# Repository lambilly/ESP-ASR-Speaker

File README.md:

# ESP-ASR-Speaker · 翻页时钟 + 离线语音 + 蓝牙音箱

> 基于 **ESP32-WROVER-E (N16R8)** 与 **ASRPRO 2.0** 的桌面智能音箱：
> 铝合金翻页时钟音箱外壳 + 离线语音识别 + HA TTS 播报 + 蓝牙 A2DP + 30 颗 WS2812 状态灯。
>
> 项目首发于『瀚思彼岸』论坛：[【阿木制作】集翻页时钟、离线语音、蓝牙音箱、TTS、WiFi 和彩灯音箱](https://bbs.hassbian.com/forum.php?mod=viewthread&tid=33323)

---

## 这个项目做了什么

一块自制的 ESP32 主板塞进现成的铝合金音箱壳里，把四件东西合成一台：

- **ESP32** 负责音频流、蓝牙接收、灯效状态机、IO 控制
- **ASRPRO** 专门做离线语音识别，识别结果通过 UART 发给 ESP32
- ESP32 再联动 **Home Assistant / Node-RED** 触发场景（说一句"关灯"，HA 执行 + TTS 回一句"好的，已为您关灯"）
- 不开 HA 也能当**普通蓝牙音箱**用

## 功能特性

| 功能 | 说明 |
|---|---|
| 离线语音输入 | ASRPRO 本地识别，不联网、隐私安全、响应快 |
| HA 语音播报 | ESPHome `media_player` 接入 HA Edge TTS 等服务，MP3 流式播放 |
| 蓝牙音箱模式 | `a2dp_sink` 组件，手机连上就放歌 |
| 翻页屏时钟 | 81×26mm 彩色翻页时钟，全时段在线显示 |
| 状态指示灯 | 30 颗 WS2812，用颜色 + 呼吸/渐变表达 9 种系统状态 |
| 物理按键 | 两颗面板键做短按/长按分层：灯带开关、亮度三档、静音、蓝牙切换 |
| 过热保护 | DS18B20 测箱内温度，>50℃ 橙色呼吸提示 |
| 电池供电 | 18650 + IP5306，Type-C 充电，拔电可用 |

🎬 效果视频：[docs/images/demo.mp4](docs/images/demo.mp4)

---

## 硬件设计

### 主要器件

| 模块 | 型号 | 作用 |
|---|---|---|
| 主控 | ESP32-WROVER-E **N16R8**（16MB Flash + 8MB PSRAM） | 音频调度、灯光、IO |
| 语音 | ASRPRO **2.0** 核心板 4M | 离线识别 + 本地 TTS |
| 功放 | MAX98357A（I2S 数字功放） | 4Ω10W 喇叭驱动 |
| 电源 | IP5306 升压充放电一体板（**需升级版常开模式，2A 以上**） | 5V 供电 + 电池充电 |
| 灯带 | WS2812 × 30（GRB） | 全系统状态指示 |
| 温度 | DS18B20 | 箱体过热保护 |
| 按键 | 12mm 带灯非自锁 ×2 + 自锁 ×1 | 灯光/亮度、静音/蓝牙、总电源 |
| 阻容 | 10kΩ ×2（按键上拉）、220Ω ×1（灯带串联）、470μF + 0.1μF（滤波） | 全直插，方便新手焊接 |

### 引脚分配

| 功能 | GPIO | 备注 |
|---|---|---|
| UART TX / RX（ASRPRO） | 14 / 13 | 115200 8N1 |
| I2S BCLK / LRCK / DOUT | 27 / 26 / 25 | MAX98357A |
| MAX98357 `SD_MODE` | 22 | 低电平 = 硬件静音 |
| WS2812 数据 | 19 | 串联 220Ω 到灯带 DIN |
| DS18B20 | 32 | 单总线，4.7K 上拉 |
| LED 键 | 34 | **必须外部 10k 上拉** |
| Mode 键 | 35 | **必须外部 10k 上拉** |

### 外壳与结构件

外壳、翻页时钟屏、WS2812 灯带都来自网上现成的**铝合金翻页时钟音箱**套件，本项目只重做了内部主板：

- 铝合金箱体 **70×70×120mm**，带透光板、透光喇叭托环、透光振膜
- 彩色翻页时钟屏 **81×26mm**
- 哈曼 4Ω10W 全频喇叭
- 18650 电池包、止震贴、配重块

> 结构件图纸（STL）后续单独放出；壳体属第三方商品，本项目不附带其图纸与商品图。
>
> 本文中的成品照片与演示视频均为作者本人拍摄，不含第三方商品图。

### PCB 状态

- 板框 **84 × 53 mm**，**2 层板**，全直插 + 拔插式核心板（方便升级）
- 原理图已通过 ERC；**布线尚未完成、GND 未铺铜，暂不提供 Gerber**，请勿直接打样
- ⚠️ 1.0 版打样板**两个开关的原理图画错了**，当时飞线解决；2.0 版板已在嘉立创下单，验证后再放工程图

用 **KiCad 10** 打开 `hardware/ESP-ASR-Speaker.kicad_pro`。

| 原理图 | PCB 预览 |
|---|---|
| [docs/schematic.pdf](docs/schematic.pdf) |  |

---

## 固件（ESPHome）

### 音频管线：单管线 + 双音源

为了把 HA TTS 和蓝牙音频塞进同一套音频栈，用 `speaker_source` 平台，把蓝牙音源与 HTTP 音源放进**同一条管线**：

```yaml
media_player:
  - platform: speaker_source
    media_pipeline:
      speaker: max98357_speaker
      sources: [ a2dp_source, http_source ]
      format: MP3
```

> 试过双管线混音，底层音频流格式必然冲突（`Incompatible audio streams`），最终改成单管线双媒体源；HA 侧强制转码 MP3 单声道。

### LED 状态对照

| 颜色 | 状态 |
|---|---|
| 白色闪烁 | 上电开机动画（亮度压到 45%，避开电源输出上限） |
| 绿色常亮 | 空闲待机 |
| 青色呼吸 | 正在拾音 LISTEN（3 秒无新指令自动回待机） |
| 彩虹渐变 | TTS 播报中 |
| 蓝色呼吸 | 蓝牙音箱模式 |
| 紫红常亮 | 已静音 |
| 橙色呼吸 | 箱内温度 > 50℃ |
| 红色**呼吸** | OTA 升级中 |
| 红色**常亮** | WiFi 掉线 |

当前优先级：**灯带关闭 > 静音 > 过热 > 蓝牙 > TTS 播报 > 待机**

### 按键

| 操作 | LED 键（GPIO34） | Mode 键（GPIO35） |
|---|---|---|
| 短按 | 开/关灯带 | 硬件静音开/关（拉低 SD_MODE） |
| 长按 ≥0.8s | 亮度循环 100% → 50% → 25% | 蓝牙模式开/关 |

### 部署

```bash
cd firmware
cp secrets.yaml.example secrets.yaml   # 填 WiFi / API 密钥
esphome run esp-asr-speaker.yaml
```

首次烧录用 USB（板型 `esp32-wrover-kit`，esp-idf 框架，PSRAM quad 80MHz），之后走 OTA。

外部组件（首次编译自动从 GitHub 拉取）：

```yaml
external_components:
  - source: github://MexHigh/ESPHome-UART-Read-Line-Sensor   # 串口按行收指令
  - source: github://PxPert/a2dp_sink@master                 # 蓝牙 A2DP 接收
```

---

## ⚠️ 避坑指南（照着做能少烧几块板）

**1. 灯带线色是反的，别按"红正黑负"接**

> 红 = **GND**，黄 = **+5V**，黑 = **DATA**

不是"红正黑负"。我第一次没查卖家说明、只问了 AI，结果**烧了灯带和带灯开关**（灯带剪掉两颗还能用，开关报废）。接线前务必量一下。

**2. GPIO34 / 35 没有内部上拉**

必须外接 10kΩ 到 3.3V，悬空会乱触发。反过来，**不要**在按键两端并 0.1μF 电容——ESPHome 的 `delayed_on: 30ms` 软件消抖足够，硬件电容反而干扰。

**3. 灯带数据线串 220Ω**

GPIO19 与灯带 DIN 之间串 220~470Ω，防止信号反射烧掉第一颗灯珠。还要确保 ESP32 与灯带**共地**。

**4. 电源别小马拉大车**

功放遇到鼓点瞬间压降会让 ESP32 直接重启。IP5306 2.4A 已经是下限，条件允许上 3A/5A 升降压模块。
MAX98357A 的 VIN–GND 就近并 **470μF 以上**电解电容，灯带供电端并 **100μF 以上**。

**5. 蓝牙断开后重连不上**

`http_request: verify_ssl: false`，并且不要在代码里反复调 `stop()`，直接用 switch 实体控制蓝牙开关。

**6. TTS 没声音**

先查 HA 的 ffmpeg 是否正常，再把 `audio_http` 的 `buffer_size` 降下来。

**7. `minimum_chip_revision: "3.1"`**

按手上这块 WROVER 的批次写死的，换芯片批次先删掉这行，否则拒刷。日志默认 `WARN`，首刷排查时临时改 `INFO`。

---

## 目录结构

```
├─ hardware/                  KiCad 工程（原理图 / PCB / 工程配置）
├─ firmware/
│  ├─ esp-asr-speaker.yaml    ESPHome 主配置
│  ├─ secrets.yaml.example    密钥模板
│  └─ components/             自定义头文件（串口指令解析 / LED 状态机）
├─ docs/
│  ├─ schematic.pdf           原理图导出
│  ├─ pcb-top.svg             PCB 预览
│  ├─ bom.csv                 元件清单（不含价格）
│  └─ images/                 成品图与演示视频
├─ LICENSE
└─ README.md
```

## 物料清单

元件清单见 [docs/bom.csv](docs/bom.csv)（型号 / 封装 / 数量，不含采购价格）。
结构件另需：70×70×120 铝合金壳体、81×26mm 翻页时钟屏、哈曼 4Ω10W 喇叭、透光振膜与托环、18650 电池、止震贴、配重块。

## 已知问题 / Roadmap

- [x] 原理图 ERC 清零、35 个元件封装分配完毕
- [ ] **完成 PCB 布线 + GND 铺铜，出 Gerber**（当前不提供打样文件）
- [ ] 2.0 版板卡验证（1.0 版两个开关原理图画错，靠飞线救回）
- [ ] 结构件 STL 图纸整理后放出
- [ ] 补 `use_address`，解决 OTA mDNS 解析问题
- [ ] 第二台复刻验证（芯片批次、按键手感）

## 致谢

- 外壳与结构件：**铝合金翻页时钟音箱**套件
- [MexHigh/ESPHome-UART-Read-Line-Sensor](https://github.com/MexHigh/ESPHome-UART-Read-Line-Sensor)
- [PxPert/a2dp_sink](https://github.com/PxPert/a2dp_sink)
- ESPHome / KiCad / 瀚思彼岸社区

## 免责声明

DIY 锂电池供电设备存在**短路起火风险**，请在接线无误、绝缘良好的前提下通电测试。作者不对任何复制过程中的损失负责。

## License

[MIT](LICENSE) © 2026 lambilly

> 固件与硬件设计文件同用 MIT。第三方件（ASRPRO 语音模型、翻页时钟模块、铝合金外壳）遵循其各自的授权。

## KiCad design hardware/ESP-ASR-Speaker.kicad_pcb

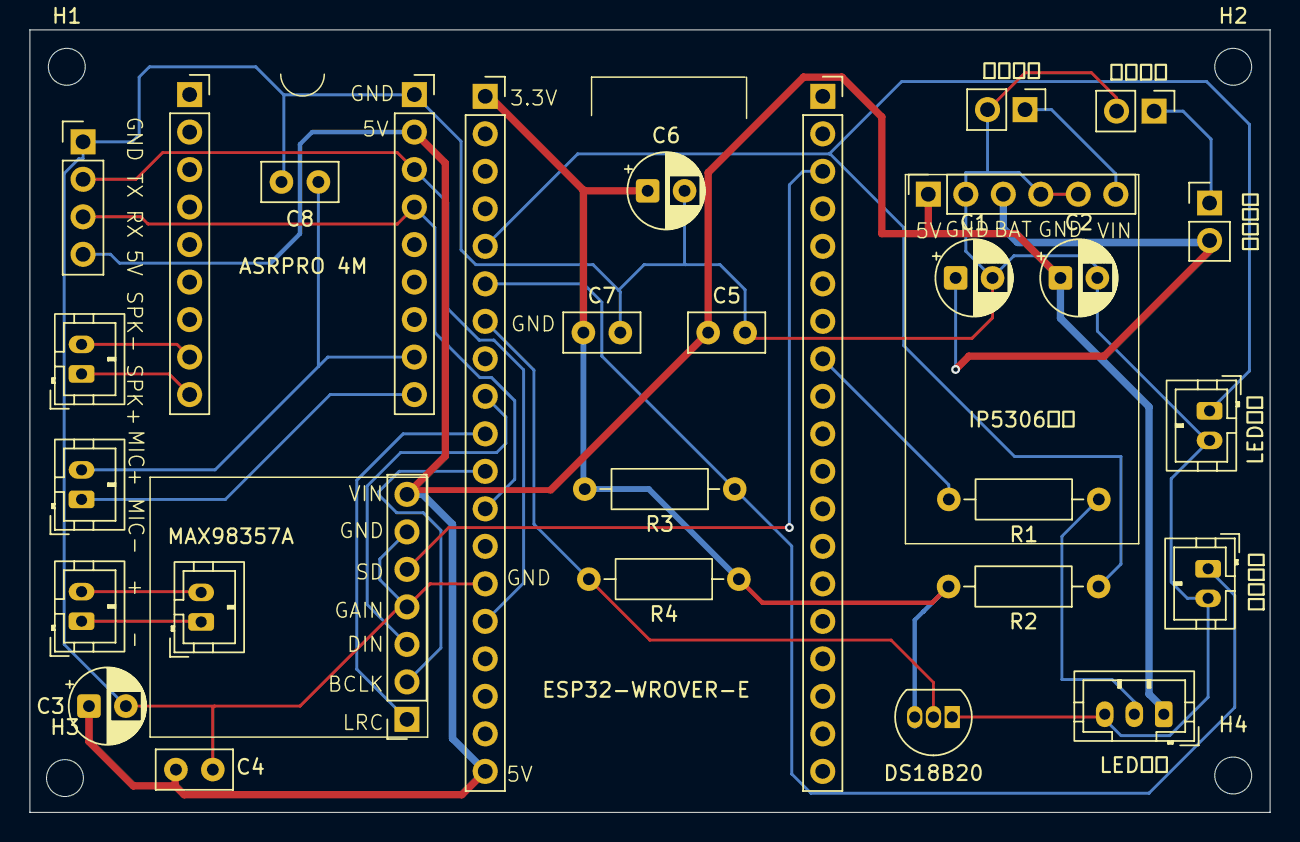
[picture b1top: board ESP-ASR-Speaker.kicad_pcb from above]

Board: 2 copper layers, 84.0 x 53.0 mm, 34 parts (0 on the bottom side), 23 nets.

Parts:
C1, C3, C6: 10μF; CP_Radial_D5.0mm_P2.50mm
C2: 22μF; CP_Radial_D5.0mm_P2.50mm
C4, C5, C7, C8: 0.1μF; C_Disc_D5.0mm_W2.5mm_P2.50mm
H1, H2, H3, H4: MountingHole; MountingHole_2.5mm
J1: MAX98357A; PinSocket_1x07_P2.54mm_Vertical
J_ASRA1: ASRPRO 4M; PinSocket_1x09_P2.54mm_Vertical
J_ASRB1: PinSocket_1x09_P2.54mm_Vertical
J_ASR_SPK1: SPK; JST_PH_B2B-PH-K_1x02_P2.00mm_Vertical
J_ASR_UART1: ASRPRO TTL; PinHeader_1x04_P2.54mm_Vertical
J_BATT1: 电池输入; PinHeader_1x02_P2.54mm_Vertical
J_BATT_SW1: 电池开关; PinHeader_1x02_P2.54mm_Vertical
J_ESPA1: ESP32-WROVER-E; PinSocket_1x19_P2.54mm_Vertical
J_ESPB1: Conn_01x19_Socket; PinSocket_1x19_P2.54mm_Vertical
J_KEY_SW1: LED开关; JST_PH_B2B-PH-K_1x02_P2.00mm_Vertical
J_KEY_SW2: 功能开关; JST_PH_B2B-PH-K_1x02_P2.00mm_Vertical
J_LED_BUS1: LED灯带; JST_PH_B3B-PH-K_1x03_P2.00mm_Vertical
J_MIC1: MIC; JST_PH_B2B-PH-K_1x02_P2.00mm_Vertical
J_POWER1: IP5306模块; PinSocket_1x06_P2.54mm_Vertical
J_SPK1: Speaker; JST_PH_B2B-PH-K_1x02_P2.00mm_Vertical
J_SPK_OUT1: Speaker; JST_PH_B2B-PH-K_1x02_P2.00mm_Vertical
J_VCC1: 电源输入; PinHeader_1x02_P2.54mm_Vertical
R1: 220Ω; R_Axial_DIN0207_L6.3mm_D2.5mm_P10.16mm_Horizontal
R2, R3: 10KΩ; R_Axial_DIN0207_L6.3mm_D2.5mm_P10.16mm_Horizontal
R4: 4.7KΩ; R_Axial_DIN0207_L6.3mm_D2.5mm_P10.16mm_Horizontal
U1: DS18B20; TO-92_Inline

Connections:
/5V_LOAD: C2.1, C3.1, C4.1, C5.1, J1.7, J_ASRB1.2, J_ASR_UART1.4, J_ESPA1.19, J_LED_BUS1.1, J_POWER1.1
/ASR_RX: J_ASRB1.4, J_ASR_UART1.3, J_ESPA1.12
/ASR_TX: J_ASRB1.3, J_ASR_UART1.2, J_ESPA1.15
/BATT: C1.1, J_BATT_SW1.2, J_POWER1.3
/BCLK: J1.2, J_ESPA1.11
/DIN: J1.3, J_ESPA1.9
/ESP_3.3V: C6.1, C7.1, J_ESPA1.1, R2.2, R3.2, R4.1, U1.3 (V_{DD})
/KEY_FUNC: J_ESPA1.6, J_KEY_SW2.1, R3.1
/KEY_LED: J_ESPA1.5, J_KEY_SW1.1, R2.1
/LRCLK: J1.1, J_ESPA1.10
/RGB_DATA: J_ESPB1.8, R1.2
/SD_MODE: J1.5, J_ESPB1.3
GND: C1.2, C2.2, C3.2, C4.2, C5.2, C6.2, C7.2, C8.2, J1.4, J1.6, J_ASRB1.1, J_ASR_UART1.1, J_BATT1.2 (BAT-), J_ESPA1.14, J_KEY_SW1.2, J_KEY_SW2.2, J_LED_BUS1.3, J_POWER1.2, J_POWER1.4, J_POWER1.5, J_VCC1.2 (GND), U1.1 (GND)
unnamed: J_ASRA1.8, J_ASR_SPK1.2 (SPK+)
unnamed: J_ASRA1.9, J_ASR_SPK1.1 (SPK-)
unnamed: C8.1, J_ASRB1.8, J_MIC1.2 (MIC+)
unnamed: J_ASRB1.9, J_MIC1.1 (MIC-)
unnamed: J_BATT1.1 (BAT+), J_BATT_SW1.1
unnamed: J_ESPA1.7, R4.2, U1.2 (DQ)
unnamed: J_LED_BUS1.2, R1.1
unnamed: J_POWER1.6, J_VCC1.1 (VCC)
unnamed: J_SPK1.1, J_SPK_OUT1.1
unnamed: J_SPK1.2, J_SPK_OUT1.2

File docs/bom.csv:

"Refs","Value","Footprint","Qty"
"C1,C3,C6","10μF/10V","Capacitor_THT:CP_Radial_D5.0mm_P2.50mm","3"
"C2","22μF/10V","Capacitor_THT:CP_Radial_D5.0mm_P2.50mm","1"
"C4,C5,C7,C8","0.1μF/50V","Capacitor_THT:C_Disc_D5.0mm_W2.5mm_P2.50mm","4"
"J1","MAX98357A","Connector_PinSocket_2.54mm:PinSocket_1x07_P2.54mm_Vertical","1"
"J_ASRA1","ASRPRO 4M","Connector_PinSocket_2.54mm:PinSocket_1x09_P2.54mm_Vertical","1"
"J_ASRB1","","Connector_PinSocket_2.54mm:PinSocket_1x09_P2.54mm_Vertical","1"
"J_ASR_SPK1","SPK","Connector_JST:JST_PH_B2B-PH-K_1x02_P2.00mm_Vertical","1"
"J_ASR_UART1","ASRPRO TTL","Connector_PinHeader_2.54mm:PinHeader_1x04_P2.54mm_Vertical","1"
"J_BATT1","电池输入","Connector_PinHeader_2.54mm:PinHeader_1x02_P2.54mm_Vertical","1"
"J_BATT_SW1","电池开关","Connector_PinHeader_2.54mm:PinHeader_1x02_P2.54mm_Vertical","1"
"J_ESPA1","ESP32-WROVER-E","Connector_PinSocket_2.54mm:PinSocket_1x19_P2.54mm_Vertical","1"
"J_ESPB1","Conn_01x19_Socket","Connector_PinSocket_2.54mm:PinSocket_1x19_P2.54mm_Vertical","1"
"J_KEY_SW1","LED开关","Connector_JST:JST_PH_B2B-PH-K_1x02_P2.00mm_Vertical","1"
"J_KEY_SW2","功能开关","Connector_JST:JST_PH_B2B-PH-K_1x02_P2.00mm_Vertical","1"
"J_LED_BUS1","LED灯带","Connector_JST:JST_PH_B3B-PH-K_1x03_P2.00mm_Vertical","1"
"J_MIC1","MIC","Connector_JST:JST_PH_B2B-PH-K_1x02_P2.00mm_Vertical","1"
"J_POWER1","IP5306模块","Connector_PinSocket_2.54mm:PinSocket_1x06_P2.54mm_Vertical","1"
"J_SPK1,J_SPK_OUT1","Speaker","Connector_JST:JST_PH_B2B-PH-K_1x02_P2.00mm_Vertical","2"
"J_VCC1","电源输入","Connector_PinHeader_2.54mm:PinHeader_1x02_P2.54mm_Vertical","1"
"R1","220Ω","Resistor_THT:R_Axial_DIN0207_L6.3mm_D2.5mm_P10.16mm_Horizontal","1"
"R2,R3","10KΩ","Resistor_THT:R_Axial_DIN0207_L6.3mm_D2.5mm_P10.16mm_Horizontal","2"
"R4","4.7KΩ","Resistor_THT:R_Axial_DIN0207_L6.3mm_D2.5mm_P10.16mm_Horizontal","1"
"U1","DS18B20","Package_TO_SOT_THT:TO-92_Inline","1"
